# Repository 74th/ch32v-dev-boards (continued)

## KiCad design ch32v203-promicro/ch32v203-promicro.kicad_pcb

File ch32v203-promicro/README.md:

# RISC-V MCU CH32V203 ProMicro Sized Dev Board

The contents of this page include the KiCad files in this repository, as well as kits sold by Booth and finished products sold by Switch Science.

Please check [Documents](#documents) for schematics, bill of materials, pin maps, etc.

🇯🇵

本ページのコンテンツは、本リポジトリの KiCad ファイル、及び Booth 販売品のキット、スイッチサイエンスでの完成品販売の内容が含まれています。

回路図、部品表、ピンマップ等については、[Documents](#documents)を確認ください。

- [CH32V203 での開発方法について](#CH32V203-の開発方法)
- キット販売ページ(BOOTH) https://74th.booth.pm/items/4492691

# main features

- Uses RISC-V CH32V203C8T6, resembling STM32.
- Pin configuration with functions similar to ProMicro (UART, I2C, SPI, ADC).
- By pressing the BOOT button while pressing RESET, it enters a mode that allows writing via USB.
- USB1DM/DP already wired to USB Port(USB2 not wired).

🇯🇵

- STM32 に似せた RISC-V CH32V203C8T6 を使用
- ProMicro に近い機能のピン配置（UART、I2C、SPI、ADC）
- BOOT ボタンを押しながら RESET を押すことで、USB で書き込みできるモードに入る
- USB には、USB1DM/DP を配線済み

# How to use 使い方

- There is a BOOT button, and by pressing the BOOT button while holding down RESET(RST), the mode is set to write via USB.
- GND on the left side is changed to SWDIO and SWCLK. Connect WCH-Link to GND, SWDIO, and SWCLK.

🇯🇵

- BOOT ボタンがあり、RESET を押しながら BOOT ボタンを押すことで、USB 経由で書き込めるモードになります。
- 左側の GND を、SWDIO、SWCLK に変更しています。こちらから WCH-Link を用いることで書き込みができるようになります。WCH-Link と GND、SWDIO、SWCLK を接続してください。

# Documents

## CH32V203Micro v1.2.1-2

- v1.2.2 と v1.2.1 の違いは利用した KiCad バージョンの更新と、若干のフットプリントの修正で、部品表、機能に違いはありません。

- semantics [PDF](./docs/ch32v203-promicro-v1.2.1.pdf) [Kicanvas](https://kicanvas.org/?github=https%3A%2F%2Fgithub.com%2F74th%2Fch32v-dev-boards%2Fblob%2Fch32v203promicro%2F1.2.1%2Fch32v203-promicro%2Fch32v203-promicro.kicad_sch)
- PCB
  - 1.2.1 [Kicanvas](https://kicanvas.org/?github=https%3A%2F%2Fgithub.com%2F74th%2Fch32v-dev-boards%2Fblob%2Fch32v203promicro%2F1.2.1%2Fch32v203-promicro%2Fch32v203-promicro.kicad_pcb)
  - 1.2.2 [Kicanvas](https://kicanvas.org/?github=https%3A%2F%2Fgithub.com%2F74th%2Fch32v-dev-boards%2Fblob%2Fch32v203promicro%2F1.2.2%2Fch32v203-promicro%2Fch32v203-promicro.kicad_pcb)

### Pin Map

### new feature

- Anticipating the use of the USB write function, the following changes have been made:
  - The X32Micro v1.2.0 added an SWD 10-pin port, but it was removed in the CH32V203Micro v1.2.1.
  - The X32Micro v1.2.0 removed the BOOT button, but it was re-added in the CH32V203Micro v1.2.1.
  - The X32Micro v1.2.0 added through-holes for BOOT0 and BOOT1, but these were removed. This is because basically only BOOT0 is used.
- Differences from X32Micro v1.1.0:
  - Added CH213K as a USB power protection IC.
  - Added damping resistors to USB DM/DP.
  - Omitted the low-power crystal oscillator (internal RC clock can be used).
  - Pin configuration change.

🇯🇵

- USB で書き込みできる機能を利用する想定で、以下の変更を行いました。
  - X32Micro v1.2.0 では SWD 10 ピンポートを追加しましたが、CH32V203Micro v1.2.1 ではを削除しました。
  - X32Micro v1.2.0 では BOOT ボタンを削除しましたが、CH32V203Micro v1.2.1 では、BOOT ボタンを再度追加しました。
  - X32Micro v1.2.0 では BOOT0、BOOT1 のスルーホールを追加しましたが、削除しました。BOOT0 しか基本的に利用されないためです。
- X32Micro v1.1.0 からの差分
  - USB 電源保護 IC として CH213K を追加
  - USB DM/DP にダンピング抵抗を追加
  - Low Power 用水晶発振器を省略（内蔵 RC クロックが使用可能）
  - ピン配置変更

### 部品表 Parts List

| Reference  | Name                                  | Quantity |
| ---------- | ------------------------------------- | -------- |
| C1, C2     | Capacitor 0805 10uF                   | 2        |
| C3         | Capacitor 0805 1uF                    | 1        |
| C4-C8      | Capacitor 0805 100nF                  | 5        |
| C9, C10    | Capacitor 0805 10-22pF                | 2        |
| D1         | LED 0805 BLUE                         | 1        |
| J1         | USB Type-C Receptacle                 | 1        |
| R1, R2     | Register 0805 5.1kΩ                   | 2        |
| R3, R6, R7 | Register 0805 10kΩ                    | 3        |
| R4, R5     | Register 0805 27Ω                     | 2        |
| SW1, SW2   | Button SKRPABE010                     | 2        |
| U1         | Regulator 3.3V SOT-89 AMS1117-3.3     | 1        |
| U2         | MCU LQFP48 WCH CH32V203C8T6           | 1        |
| U3         | USB Power Protection IC SOT-23 CH213K | 1        |
| Y1         | Crystal 3225 8MHz                     | 1        |

## X32Micro v1.2.0

Please see [https://github.com/74th/x32promicro?tab=readme-ov-file#x32micro-v120](https://github.com/74th/x32promicro?tab=readme-ov-file#x32micro-v120).

## X32Micro v1.1.0

### 部品表 Parts List

| Reference | Parts                                       | Qty |
| --------- | ------------------------------------------- | --- |
| C1-C3, C6 | 0805 Capacitor 100n                         | 4   |
| C4        | 0805 Capacitor 10u                          | 1   |
| C5        | 0805 Capacitor 2.2u                         | 1   |
| C7, C8    | 0805 Capacitor 12p                          | 2   |
| C9, C10   | 0805 Capacitor 22p                          | 2   |
| R1        | 0805 Resister 200                           | 1   |
| R2        | NC or 0805 Resister 10k for BOOT0 Pull Up   | 1   |
| R8        | NC or 0805 Resister 10k for BOOT0 Pull Down | 1   |
| R6-R7     | 0805 Resister 10k                           | 2   |
| R3        | 0805 Resister 0 R                           | 1   |
| R4, R5    | 0805 Resister 5.1k                          | 2   |
| D1        | 0805 LED                                    | 1   |
| J1        | USB2.0 Socket                               | 1   |
| JP1       | Jumper BOOT SW Pull Up / Down               | 1   |
| SW1, SW2  | SW Push                                     | 2   |
| U1        | MCU STM32V103C8T6                           | 1   |
| U2        | SOT-89 Regulator AMS1117-3.3                | 1   |
| Y1        | 3215 Oscillator 32.768k                     | 1   |
| Y2        | 3225 Oscillator 8M                          | 1   |

- CH32V203 など BOOT0 を Pull Up し、BOOT スイッチで GND に繋ぎたい場合
  - R2 を実装してください
  - R8 は未実装 NC にしてください
  - JP1 の中央のランドを △ マークにジャンパしてください
- STM32F103 など BOOT0 を Pull Down し、BOOT スイッチで 3V3 に繋ぎたい場合
  - R2 は未実装 NC にしてください
  - R8 を実装してください
  - JP1 の中央のランドを + マークにジャンパしてください

## CH32V203Micro v1.0.0

- BOOTH 販売ページ
- 回路図 Semantics [docs/ch32v203-promicro-v1.0.0-semantics.pdf](docs/ch32v203-promicro-v1.0.0-semantics.pdf)
- PCB [docs/ch32v203-promicro-v1.0.0-pcb.pdf](docs/ch32v203-promicro-v1.0.0-pcb.pdf)

### 部品表 Parts List

| Reference | Parts                             | num |
| --------- | --------------------------------- | --- |
| C1-C3,C6  | 0805 Capacitor 100nF              | 4   |
| C4        | 0805 Capacitor 10uF               | 1   |
| C5        | 0805 Capacitor 2.2uF              | 1   |
| C7,C8     | 0805 Capacitor 12pF               | 2   |
| C9,C10    | 0805 Capacitor 22pF               | 2   |
| D1        | 0805 LED                          | 1   |
| J1        | USB Type-C Socket                 | 1   |
| J2        | PinHeader                         | 1   |
| J3        | PinHeader                         | 1   |
| R1        | 0805 Register 200R                | 1   |
| R2,R6,R7  | 0805 Register 10kR                | 3   |
| R3        | 0805 Register 0R                  | 1   |
| R4,R5     | 0805 Register 5.1k                | 2   |
| SW1       | SW Push                           | 2   |
| U1        | MCU CH32V203CxT6                  | 1   |
| U2        | SOT-89 3.3V Regulator AMS1117-3.3 | 1   |
| Y1        | 3215 Oscillator 32.768kHz         | 1   |
| Y2        | 3225 Oscillator 8MB               | 1   |

# CH32V203 の開発方法

## CH32V203 のファームウェアの書き込み方法

### 1. USB で書き込み場合

BOOT を押しながら、RESET を押すと、USB で書き込みを受け付けるモードになります。このモード中では、以下のソフトウェアを用いて書き込みが可能です。

- WCHISP Tool(公式) : https://www.wch-ic.com/downloads/WCHISPTool_Setup_exe.html
  - GUI で操作するツール
  - Windows のみ
- wchisp(ch32-rs) : https://github.com/ch32-rs/wchisp
  - CLI ツール

私 74th としては、wchisp が、Linux でも動作するため、便利でお勧めです。以下のようにして、書き込みます。

```
wchisp flash release/ch32v203c8t6.elf
```

### 2. WCH-Link を用いる場合

WCH-Link と SWDIO、SWCLK を接続してください。

WCH-Link を用いる場合の書き込みソフトウェアとして、以下があります。

- WCH-LinkUtility(公式) : https://www.wch.cn/downloads/WCH-LinkUtility_ZIP.html
  - GUI で操作するツール
  - Windows のみ
- minichlink(ch32v003fun) : https://github.com/cnlohr/ch32v003fun/tree/master/minichlink
  - CLI ツール
- wlink(ch32-rs) : https://github.com/ch32-rs/wlink
  - CLI ツール
- OpenOCD(WCH によるフォーク): MounRiverStudio に含まれる http://www.mounriver.com/download
  - CLI ツール

74th としては、wlink が、Linux でも動作するため、便利でお勧めです。

```
wlink flash release/ch32v203c8t6.elf
```

## CH32V203 の開発環境

PlatformIO(VS Code)を使った開発の方法を記事にしています

> WCH の RISC-V マイコン CH32V を公式 SDK を使って、VS Code の PlatformIO で開発する - @74th の制作ログ
>
> https://74th.hateblo.jp/entry/ch32v-platformio

CH32V203 の開発フレームワークとして以下が利用可能です。

- 公式 SDK: https://github.com/openwch/ch32v20x/tree/main/C%2B%2B/Use%20MRS%20Create%20C%2B%2B%20project-example/CH32V203C8T6%2B%2B
  - C/C++
  - STM32 の古い SDK 似
- ch32-rs: https://github.com/ch32-rs/ch32-rs
  - Rust のペリフェラルアクセスクレート
- WCH 提供 Arduino: https://github.com/openwch/arduino_core_ch32

開発環境としては、以下が利用できます。

- MounRiverStudio(公式): http://www.mounriver.com/download
  - 公式 SDK を利用
  - Windows、Linux のみ
- PlatformIO(コミュニティメンテ) : https://github.com/Community-PIO-CH32V/platform-ch32v
  - 公式 SDK を利用
  - MounRiverStudio に含まれる GNU ライセンスの gcc、OpenOCD 等を取り込んでいる
  - gcc、OpenOCD は x64 のみ（ARM CPU では動作不可）
- Rust(ch32v-rs 利用)
- Arduino IDE: https://github.com/openwch/arduino_core_ch32
- 公式 SDK 用 Makefile テンプレート: https://github.com/cjacker/ch32v_evt_makefile_gcc_project_template

74th としては PlatformIO が、環境構築がお手軽でお勧めです。ただし、AMD64 CPU でないと動作しません。

CH32V203 は、RV32IMAC に独自拡張命令を含んだ RV32IMACXW という命令セットを使っています。そのため、公式が提供する GCC でないと正常にコンパイルできないことがあります。

## 開発方法についてのブログ記事等情報

### 74th のブログ記事

- WCH の RISC-V マイコン CH32V を公式 SDK を使って、VS Code の PlatformIO で開発する https://74th.hateblo.jp/entry/ch32v-platformio
- WCH の RISC-V MCU CH32V203 を Rust で L チカする https://74th.hateblo.jp/entry/2022/12/22/223956

### その他記事

- オープンソースツールチェインでの CH32V の開発方法（英語） https://github.com/cjacker/opensource-toolchain-ch32v
- VSCode+PlatformIO で RISC-V CH32V203 マイコンの開発環境を構築 https://zenn.dev/usagi1975/articles/2023-09-30-0002_ch32v-platformio

### 公式ドキュメント

- データシート https://www.wch-ic.com/downloads/CH32V20x_30xDS0_PDF.html
- リファレンスマニュアル https://www.wch-ic.com/downloads/CH32FV2x_V3xRM_PDF.html
- C/C++ SDK https://github.com/openwch/ch32v20x/tree/main/C%2B%2B/Use%20MRS%20Create%20C%2B%2B%20project-example/CH32V203C8T6%2B%2B

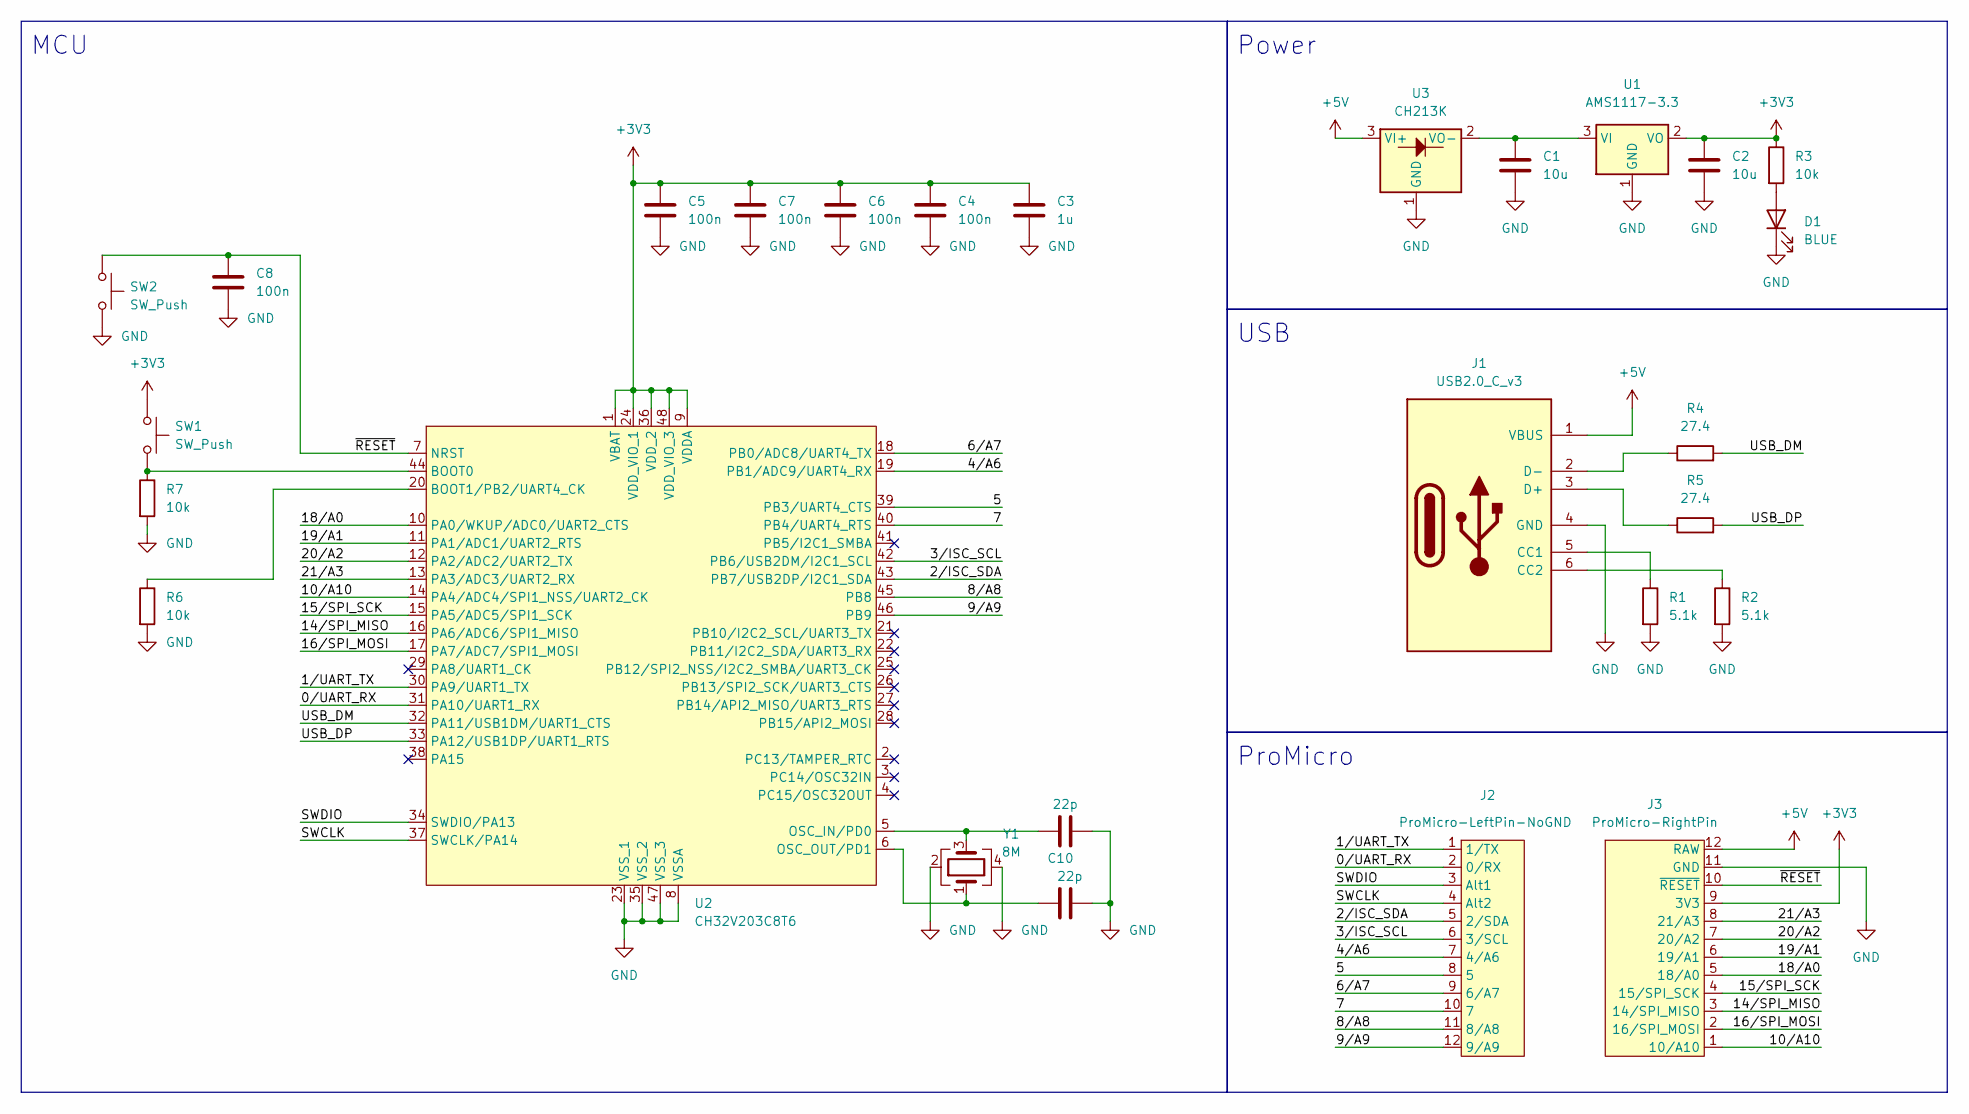
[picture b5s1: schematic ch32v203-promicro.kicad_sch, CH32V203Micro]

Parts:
C1, C2: 10u; Capacitor_0805_2012
C3: 1u; Capacitor_0805_2012
C4, C5, C6, C7, C8: 100n; Capacitor_0805_2012
C9, C10: 22p; Capacitor_0805_2012
D1: BLUE; LED_0805_2012
J1: USB2.0_C_v3; Connector_USB-C-Receptacle_SMT_12-Pin_Simple
J2: ProMicro-LeftPin-NoGND; PinOut_ProMicro-LIKE_LEFT_NO-GND
J3: ProMicro-RightPin; PinOut_ProMicro-LIKE_RIGHT
R1, R2: 5.1k; Register_0805_2012
R3, R6, R7: 10k; Register_0805_2012
R4, R5: 27.4; Register_0805_2012
SW1, SW2: SW_Push; Switch_SKRPABE010
U1: AMS1117-3.3; Package_SOT-89-3
U2: CH32V203C8T6; Package_LQFP-48_7x7mm_P0.5mm
U3: CH213K; Package_SOT-23
Y1: 8M; Crystal_SMD_3225-4Pin_3.2x2.5mm_HandSoldering

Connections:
+3V3: C2.1, C3.1, C4.1, C5.1, C6.1, C7.1, J3.9 (3V3), R3.1, SW1.1, U1.2 (VO), U2.1 (VBAT), U2.9 (VDDA), U2.24 (VDD_VIO_1), U2.36 (VDD_2), U2.48 (VDD_VIO_3)
+5V: J1.1 (VBUS), J3.12 (RAW), U3.3 (VI+)
/0/UART_RX: J2.2 (0/RX), U2.31 (PA10/UART1_RX)
/1/UART_TX: J2.1 (1/TX), U2.30 (PA9/UART1_TX)
/2/ISC_SDA: J2.5 (2/SDA), U2.43 (PB7/USB2DP/I2C1_SDA)
/3/ISC_SCL: J2.6 (3/SCL), U2.42 (PB6/USB2DM/I2C1_SCL)
/4/A6: J2.7 (4/A6), U2.19 (PB1/ADC9/UART4_RX)
/5: J2.8 (5), U2.39 (PB3/UART4_CTS)
/6/A7: J2.9 (6/A7), U2.18 (PB0/ADC8/UART4_TX)
/7: J2.10 (7), U2.40 (PB4/UART4_RTS)
/8/A8: J2.11 (8/A8), U2.45 (PB8)
/9/A9: J2.12 (9/A9), U2.46 (PB9)
/10/A10: J3.1 (10/A10), U2.14 (PA4/ADC4/SPI1_NSS/UART2_CK)
/14/SPI_MISO: J3.3 (14/SPI_MISO), U2.16 (PA6/ADC6/SPI1_MISO)
/15/SPI_SCK: J3.4 (15/SPI_SCK), U2.15 (PA5/ADC5/SPI1_SCK)
/16/SPI_MOSI: J3.2 (16/SPI_MOSI), U2.17 (PA7/ADC7/SPI1_MOSI)
/18/A0: J3.5 (18/A0), U2.10 (PA0/WKUP/ADC0/UART2_CTS)
/19/A1: J3.6 (19/A1), U2.11 (PA1/ADC1/UART2_RTS)
/20/A2: J3.7 (20/A2), U2.12 (PA2/ADC2/UART2_TX)
/21/A3: J3.8 (21/A3), U2.13 (PA3/ADC3/UART2_RX)
/SWCLK: J2.4 (Alt2), U2.37 (SWCLK/PA14)
/SWDIO: J2.3 (Alt1), U2.34 (SWDIO/PA13)
/USB_DM: R4.2, U2.32 (PA11/USB1DM/UART1_CTS)
/USB_DP: R5.2, U2.33 (PA12/USB1DP/UART1_RTS)
/~RESET: C8.1, J3.10 (~RESET), SW2.1, U2.7 (NRST)
GND: C1.2, C2.2, C3.2, C4.2, C5.2, C6.2, C7.2, C8.2, C9.2, C10.2, D1.1 (K), J1.4 (GND), J3.11 (GND), R1.2, R2.2, R6.2, R7.2, SW2.2, U1.1 (GND), U2.8 (VSSA), U2.23 (VSS_1), U2.35 (VSS_2), U2.47 (VSS_3), U3.1 (GND), Y1.2, Y1.4
unnamed: D1.2 (A), R3.2
unnamed: J1.5 (CC1), R1.1
unnamed: J1.6 (CC2), R2.1
unnamed: J1.3 (D+), R5.1
unnamed: J1.2 (D-), R4.1
unnamed: C1.1, U1.3 (VI), U3.2 (VO-)
unnamed: R7.1, SW1.2, U2.44 (BOOT0)
unnamed: R6.1, U2.20 (BOOT1/PB2/UART4_CK)
unnamed: C9.1, U2.5 (OSC_IN/PD0), Y1.3
unnamed: C10.1, U2.6 (OSC_OUT/PD1), Y1.1

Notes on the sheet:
USB
ProMicro
MCU
Power

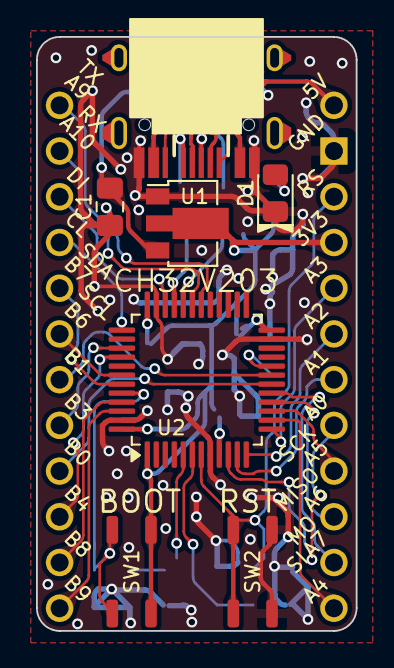
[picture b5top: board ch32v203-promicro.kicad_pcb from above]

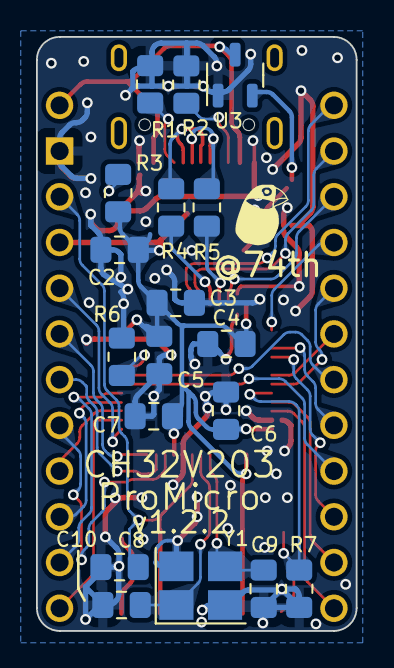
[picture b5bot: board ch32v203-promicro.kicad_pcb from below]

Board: 2 copper layers, 17.8 x 33.0 mm, 28 parts (19 on the bottom side), 36 nets.

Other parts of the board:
MISC-ICON: LOGO; 74th-4mm

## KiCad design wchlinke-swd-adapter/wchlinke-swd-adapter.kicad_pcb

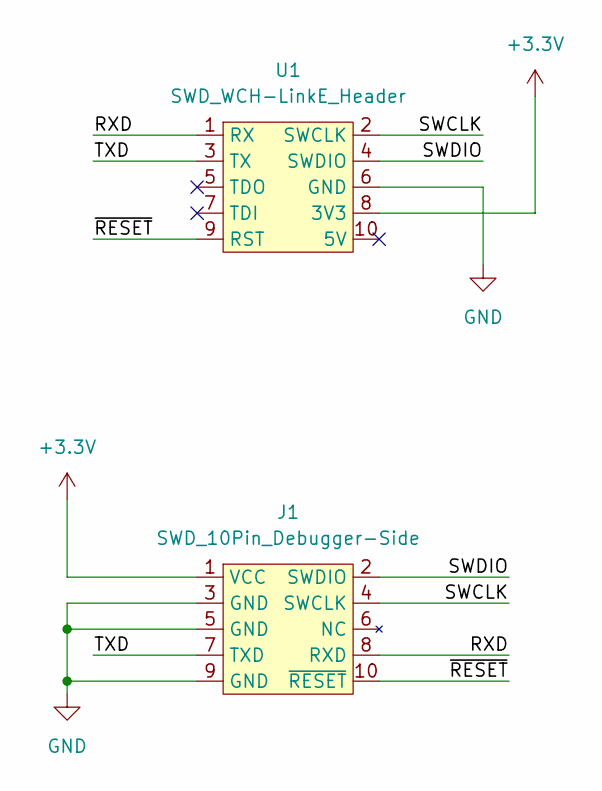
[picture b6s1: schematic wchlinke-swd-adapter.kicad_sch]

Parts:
J1: SWD_10Pin_Debugger-Side; Connector_BoxPinHeader_2x05_P1.27mm
U1: SWD_WCH-LinkE_Header; PinOut_Side_2x5P_Left_Reverse

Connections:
+3.3V: J1.1 (VCC), U1.8 (3V3)
/RXD: J1.8 (RXD), U1.1 (RX)
/SWCLK: J1.4 (SWCLK), U1.2 (SWCLK)
/SWDIO: J1.2 (SWDIO), U1.4 (SWDIO)
/TXD: J1.7 (TXD), U1.3 (TX)
/~RESET: J1.10 (~RESET), U1.9 (RST)
GND: J1.3 (GND), J1.5 (GND), J1.9 (GND), U1.6 (GND)

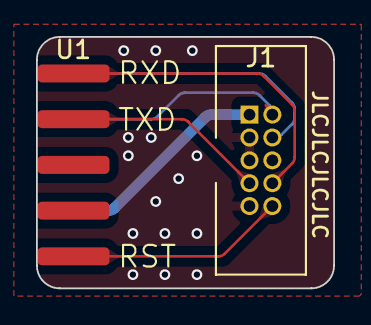
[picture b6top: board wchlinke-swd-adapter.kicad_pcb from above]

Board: 2 copper layers, 16.5 x 14.0 mm, 3 parts (1 on the bottom side), 7 nets.

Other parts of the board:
MISC-ICON: LOGO; Logo_74th_4mm

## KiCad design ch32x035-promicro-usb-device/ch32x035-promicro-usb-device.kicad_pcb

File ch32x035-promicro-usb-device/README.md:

# CH32X035 for USB-Device ProMicro

## v1.0.0

### BOM

| Reference | Name                                     | Quantity |
| --------- | ---------------------------------------- | -------- |
| C1, C2    | Capacitor 0603 10uF                      | 2        |
| C3        | Capacitor 0603 1uF                       | 1        |
| C4        | Capacitor 0603 100nF                     | 1        |
| D1        | LED 0805 BLUE                            | 1        |
| J1        | USB Type-C Receptacle                    | 1        |
| J2        | Box Pin Header 2x5 Pitch 1.27mm          | 1        |
| JP1       | Jumper Jumper_2_Open                     | 1        |
| R1, R2    | Register 0603 5.1kΩ                      | 2        |
| R3        | Register 0603 100kΩ                      | 1        |
| R4        | Register 0603 1.5kΩ                      | 1        |
| R5, R8    | Register 0603 10kΩ                       | 2        |
| R6, R7    | Register 0603 27Ω                        | 2        |
| SW1       | Button SKRPABE010                        | 1        |
| U1        | Regulator 3.3V SOT-89 AMS1117-3.3        | 1        |
| U2        | MCU QFN28 WCH CH32X035G8U6               | 1        |
| U3        | USB Power Protection IC SOT-23-6L CH217K | 1        |

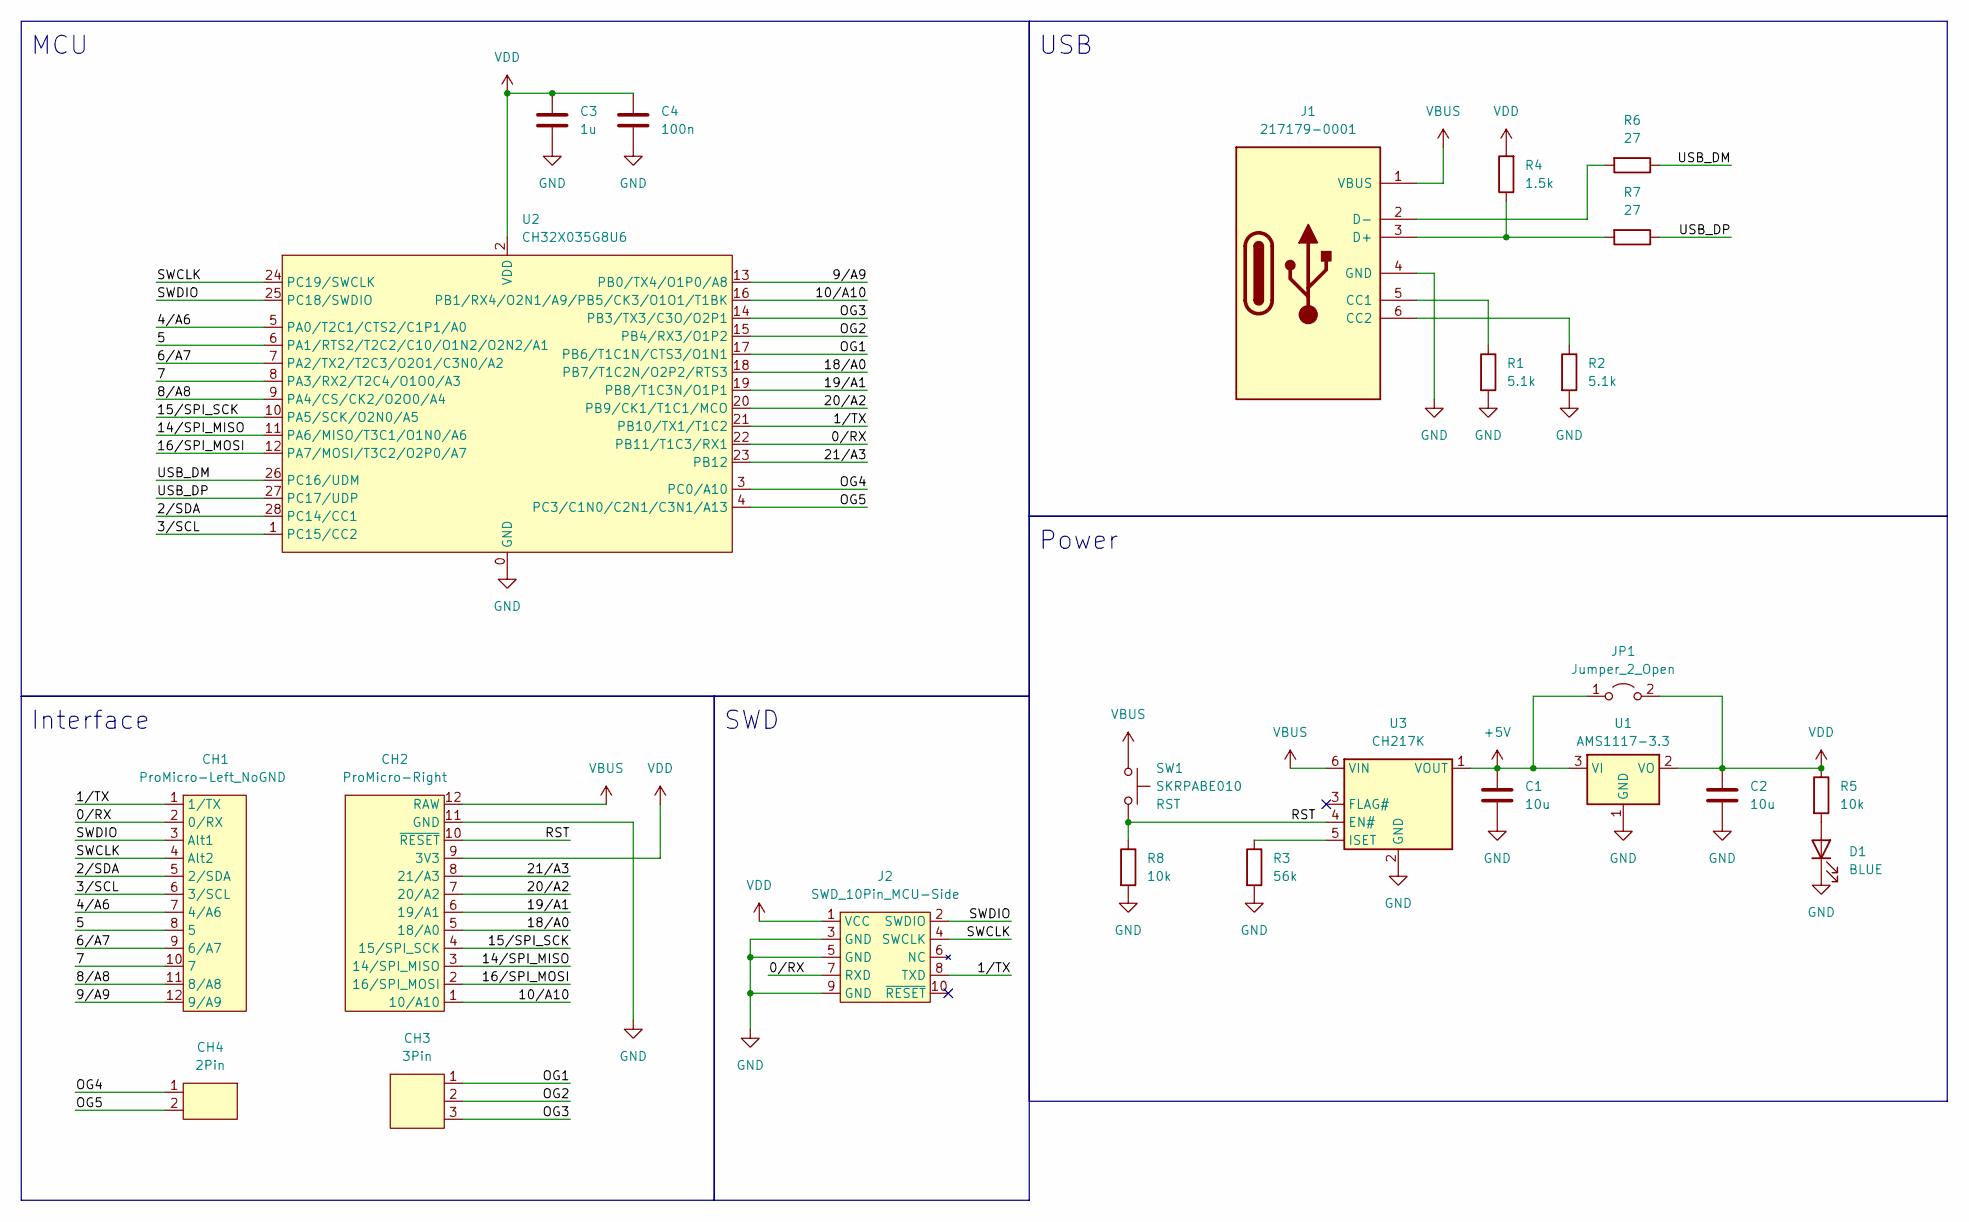
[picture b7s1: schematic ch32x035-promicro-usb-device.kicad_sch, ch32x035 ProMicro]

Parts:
C1, C2: 10u; Capacitor_0603_1608
C3: 1u; Capacitor_0603_1608
C4: 100n; Capacitor_0603_1608
CH1: ProMicro-Left_NoGND; PinOut_ProMicro-LIKE_LEFT_NO-GND
CH2: ProMicro-Right; PinOut_ProMicro-LIKE_RIGHT
CH3: 3Pin; PinOut_3Pin
CH4: 2Pin; PinOut_2Pin
D1: BLUE; LED_0805_2012
J1: 217179-0001; Connector_USB-C-Receptacle_SMT_12-Pin_Simple
J2: SWD_10Pin_MCU-Side; Connector_HalfPinHeader_SWD
JP1: Jumper_2_Open; SolderJumper-2_P1.3mm_Open_RoundedPad1.0x1.5mm
R1, R2: 5.1k; Register_0603_1608
R3: 56k; Register_0603_1608
R4: 1.5k; Register_0603_1608
R5, R8: 10k; Register_0603_1608
R6, R7: 27; Register_0603_1608
SW1: SKRPABE010; PushButton_SKRPABE010
U1: AMS1117-3.3; SOT-89-3
U2: CH32X035G8U6; Package_QFN-28-1EP_4x4mm_P0.4mm_EP2.8x2.8mm
U3: CH217K; SOT-23-6

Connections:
+5V: C1.1, JP1.1 (A), U1.3 (VI), U3.1 (VOUT)
/0/RX: CH1.2 (0/RX), J2.7 (RXD), U2.22 (PB11/T1C3/RX1)
/1/TX: CH1.1 (1/TX), J2.8 (TXD), U2.21 (PB10/TX1/T1C2)
/2/SDA: CH1.5 (2/SDA), U2.28 (PC14/CC1)
/3/SCL: CH1.6 (3/SCL), U2.1 (PC15/CC2)
/4/A6: CH1.7 (4/A6), U2.5 (PA0/T2C1/CTS2/C1P1/A0)
/5: CH1.8 (5), U2.6 (PA1/RTS2/T2C2/C10/O1N2/O2N2/A1)
/6/A7: CH1.9 (6/A7), U2.7 (PA2/TX2/T2C3/O2O1/C3N0/A2)
/7: CH1.10 (7), U2.8 (PA3/RX2/T2C4/O1O0/A3)
/8/A8: CH1.11 (8/A8), U2.9 (PA4/CS/CK2/O2O0/A4)
/9/A9: CH1.12 (9/A9), U2.13 (PB0/TX4/O1P0/A8)
/10/A10: CH2.1 (10/A10), U2.16 (PB1/RX4/O2N1/A9/PB5/CK3/O1O1/T1BK)
/14/SPI_MISO: CH2.3 (14/SPI_MISO), U2.11 (PA6/MISO/T3C1/O1N0/A6)
/15/SPI_SCK: CH2.4 (15/SPI_SCK), U2.10 (PA5/SCK/O2N0/A5)
/16/SPI_MOSI: CH2.2 (16/SPI_MOSI), U2.12 (PA7/MOSI/T3C2/O2P0/A7)
/18/A0: CH2.5 (18/A0), U2.18 (PB7/T1C2N/O2P2/RTS3)
/19/A1: CH2.6 (19/A1), U2.19 (PB8/T1C3N/O1P1)
/20/A2: CH2.7 (20/A2), U2.20 (PB9/CK1/T1C1/MCO)
/21/A3: CH2.8 (21/A3), U2.23 (PB12)
/OG1: CH3.1, U2.17 (PB6/T1C1N/CTS3/O1N1)
/OG2: CH3.2, U2.15 (PB4/RX3/O1P2)
/OG3: CH3.3, U2.14 (PB3/TX3/C3O/O2P1)
/OG4: CH4.1, U2.3 (PC0/A10)
/OG5: CH4.2, U2.4 (PC3/C1N0/C2N1/C3N1/A13)
/RST: CH2.10 (~RESET), R8.1, SW1.2, U3.4 (EN#)
/SWCLK: CH1.4 (Alt2), J2.4 (SWCLK), U2.24 (PC19/SWCLK)
/SWDIO: CH1.3 (Alt1), J2.2 (SWDIO), U2.25 (PC18/SWDIO)
/USB_DM: R6.1, U2.26 (PC16/UDM)
/USB_DP: R7.1, U2.27 (PC17/UDP)
GND: C1.2, C2.2, C3.2, C4.2, CH2.11 (GND), D1.1 (K), J1.4 (GND), J2.3 (GND), J2.5 (GND), J2.9 (GND), R1.2, R2.2, R3.2, R8.2, U1.1 (GND), U2.0 (GND), U3.2 (GND)
unnamed: D1.2 (A), R5.2
unnamed: J1.5 (CC1), R1.1
unnamed: J1.6 (CC2), R2.1
unnamed: J1.3 (D+), R4.1, R7.2
unnamed: J1.2 (D-), R6.2
unnamed: R3.1, U3.5 (ISET)
VBUS: CH2.12 (RAW), J1.1 (VBUS), SW1.1, U3.6 (VIN)
VDD: C2.1, C3.1, C4.1, CH2.9 (3V3), J2.1 (VCC), JP1.2 (B), R4.2, R5.1, U1.2 (VO), U2.2 (VDD)

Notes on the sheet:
MCU
USB
Power
Interface
SWD

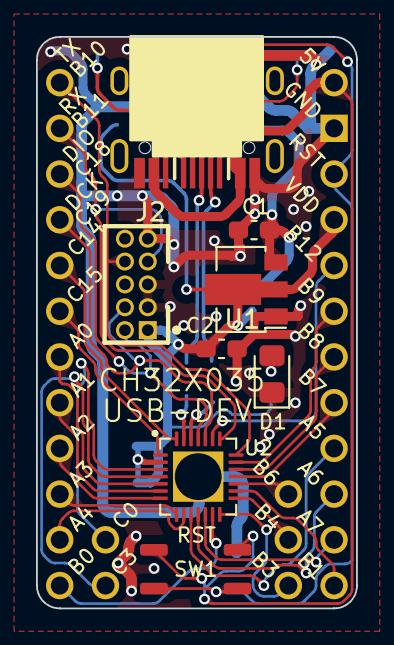
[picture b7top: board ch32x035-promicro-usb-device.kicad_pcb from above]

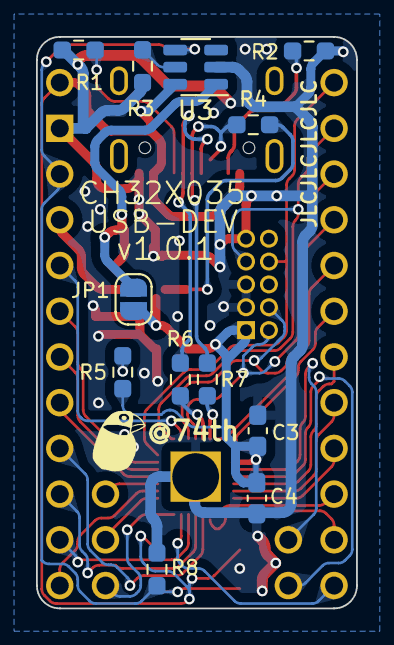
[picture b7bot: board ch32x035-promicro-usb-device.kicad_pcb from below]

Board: 2 copper layers, 17.8 x 31.8 mm, 26 parts (14 on the bottom side), 38 nets.

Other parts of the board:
MISC-ACCOUNTTEXT: Logo_74th_text
MISC-ICON: LOGO; Logo_74th_4mm

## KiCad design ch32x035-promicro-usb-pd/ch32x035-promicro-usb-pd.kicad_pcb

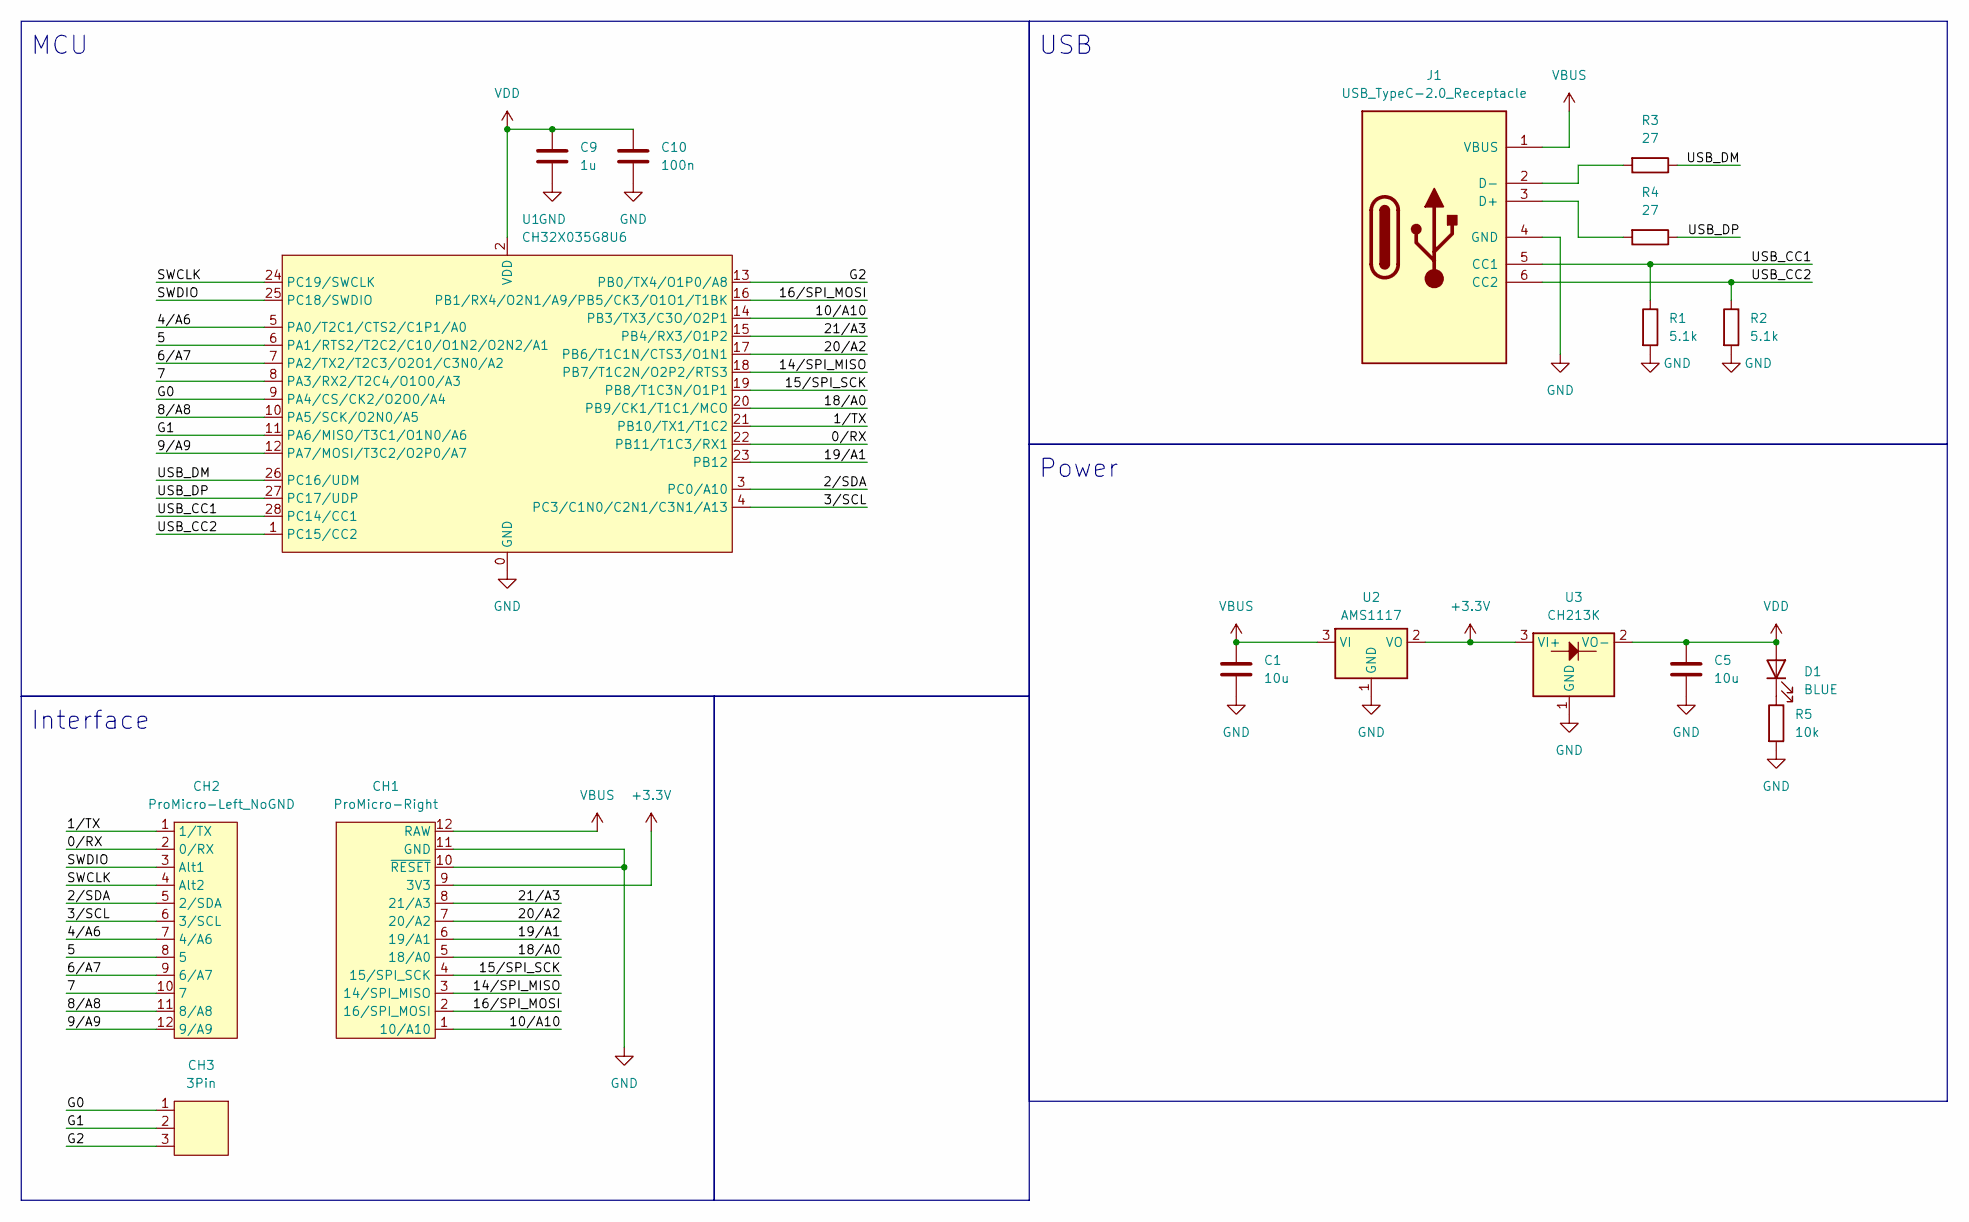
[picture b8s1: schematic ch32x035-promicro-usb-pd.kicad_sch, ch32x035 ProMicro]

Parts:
C1, C5: 10u; Capacitor_0805_2012
C9: 1u; Capacitor_0805_2012
C10: 100n; Capacitor_0805_2012
CH1: ProMicro-Right; PinOut_ProMicro-LIKE_RIGHT
CH2: ProMicro-Left_NoGND; PinOut_ProMicro-LIKE_LEFT_NO-GND
CH3: 3Pin; PinOut_3Pin
D1: BLUE; LED_0805_2012
J1: USB_TypeC-2.0_Receptacle; Connector_USB-C-Receptacle_SMT_12-Pin_Simple
R1, R2: 5.1k; Register_0805_2012
R3, R4: 27; Register_0805_2012
R5: 10k; Register_0805_2012
U1: CH32X035G8U6; Package_QFN-28-1EP_4x4mm_P0.4mm_EP2.8x2.8mm
U2: AMS1117; SOT-89-3
U3: CH213K; SOT-23

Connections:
+3.3V: CH1.9 (3V3), U2.2 (VO), U3.3 (VI+)
/0/RX: CH2.2 (0/RX), U1.22 (PB11/T1C3/RX1)
/1/TX: CH2.1 (1/TX), U1.21 (PB10/TX1/T1C2)
/2/SDA: CH2.5 (2/SDA), U1.3 (PC0/A10)
/3/SCL: CH2.6 (3/SCL), U1.4 (PC3/C1N0/C2N1/C3N1/A13)
/4/A6: CH2.7 (4/A6), U1.5 (PA0/T2C1/CTS2/C1P1/A0)
/5: CH2.8 (5), U1.6 (PA1/RTS2/T2C2/C10/O1N2/O2N2/A1)
/6/A7: CH2.9 (6/A7), U1.7 (PA2/TX2/T2C3/O2O1/C3N0/A2)
/7: CH2.10 (7), U1.8 (PA3/RX2/T2C4/O1O0/A3)
/8/A8: CH2.11 (8/A8), U1.10 (PA5/SCK/O2N0/A5)
/9/A9: CH2.12 (9/A9), U1.12 (PA7/MOSI/T3C2/O2P0/A7)
/10/A10: CH1.1 (10/A10), U1.14 (PB3/TX3/C3O/O2P1)
/14/SPI_MISO: CH1.3 (14/SPI_MISO), U1.18 (PB7/T1C2N/O2P2/RTS3)
/15/SPI_SCK: CH1.4 (15/SPI_SCK), U1.19 (PB8/T1C3N/O1P1)
/16/SPI_MOSI: CH1.2 (16/SPI_MOSI), U1.16 (PB1/RX4/O2N1/A9/PB5/CK3/O1O1/T1BK)
/18/A0: CH1.5 (18/A0), U1.20 (PB9/CK1/T1C1/MCO)
/19/A1: CH1.6 (19/A1), U1.23 (PB12)
/20/A2: CH1.7 (20/A2), U1.17 (PB6/T1C1N/CTS3/O1N1)
/21/A3: CH1.8 (21/A3), U1.15 (PB4/RX3/O1P2)
/G0: CH3.1, U1.9 (PA4/CS/CK2/O2O0/A4)
/G1: CH3.2, U1.11 (PA6/MISO/T3C1/O1N0/A6)
/G2: CH3.3, U1.13 (PB0/TX4/O1P0/A8)
/SWCLK: CH2.4 (Alt2), U1.24 (PC19/SWCLK)
/SWDIO: CH2.3 (Alt1), U1.25 (PC18/SWDIO)
/USB_CC1: J1.5 (CC1), R1.1, U1.28 (PC14/CC1)
/USB_CC2: J1.6 (CC2), R2.1, U1.1 (PC15/CC2)
/USB_DM: R3.1, U1.26 (PC16/UDM)
/USB_DP: R4.1, U1.27 (PC17/UDP)
GND: C1.2, C5.2, C9.2, C10.2, CH1.10 (~RESET), CH1.11 (GND), J1.4 (GND), R1.2, R2.2, R5.2, U1.0 (GND), U2.1 (GND), U3.1 (GND)
unnamed: D1.1 (K), R5.1
unnamed: J1.3 (D+), R4.2
unnamed: J1.2 (D-), R3.2
VBUS: C1.1, CH1.12 (RAW), J1.1 (VBUS), U2.3 (VI)
VDD: C5.1, C9.1, C10.1, D1.2 (A), U1.2 (VDD), U3.2 (VO-)

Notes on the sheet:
MCU
USB
Power
Interface

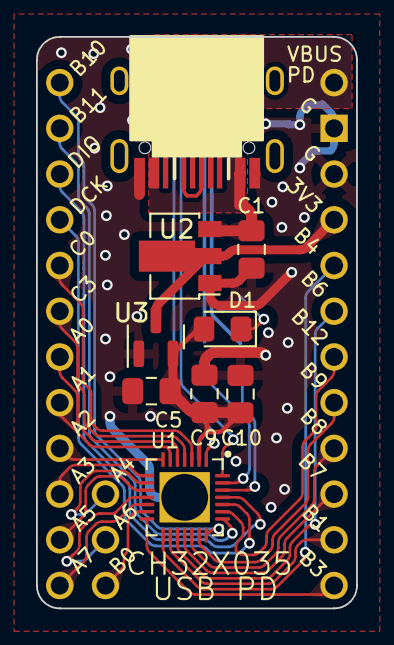
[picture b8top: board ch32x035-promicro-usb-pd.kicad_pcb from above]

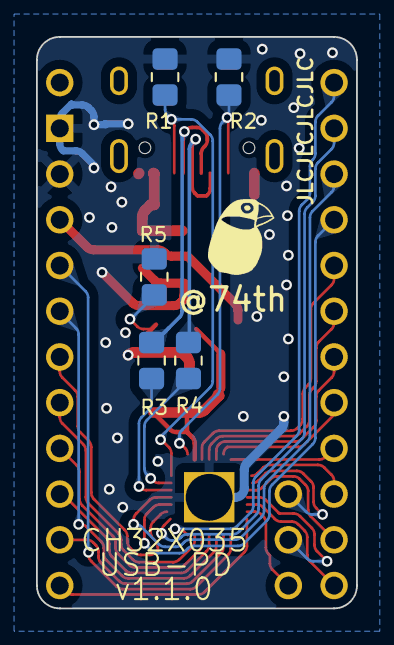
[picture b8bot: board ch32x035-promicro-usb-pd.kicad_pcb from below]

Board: 2 copper layers, 17.8 x 31.8 mm, 19 parts (7 on the bottom side), 34 nets.

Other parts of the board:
MISC-ACCOUNTTEXT: Logo_74th_text
MISC-ICON: LOGO; Logo_74th_5mm

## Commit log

2022-12-24 add symbols
2022-12-24 add symbol
2022-12-25 promicro
2022-12-25 ch32v203 promicro
2022-12-26 ch32v203micro
2022-12-26 ch32v203micro v1.0.0
2022-12-26 ch32v001 mincro
2022-12-27 ch32v003micro v1.0.0
2023-01-24 stm32
2023-01-28 x32micro v1.1.0
2023-03-01 ch32v003promicro/1.0.0
2023-03-26 add DataSheet
2023-08-17 ch32v003promicro/1.1.0
2023-09-15 v1.2.0
2023-09-18 add ch32x035
2023-09-27 ch32v203 promicro v1.2.1
2023-09-28 ch32x035-usb-device
2023-10-01 ch32x035
2023-10-17 fix SWDIO/SWCLK
2023-11-10 ch32x035-usb-pd
2023-11-10 ch32v003promicro/1.2.0
2024-01-04 ファイル移動
2024-01-11 pinout picture
2024-01-13 update document
2024-01-13 WCH LinkE SWD Adapter
2024-08-02 update kicad version
2025-02-24 ch32v00x-soic8/1.0.0
2025-02-24 ch32v006-full/1.0.0
2025-03-17 ch32v003promicto/1.3.0
2025-03-30 fix silk
2025-03-30 Add color specifications to PCB layers and update README with images
2025-05-24 ch32v00x/v1.3.1
2025-05-24 revert to ch32v003 v1.2.0
2025-05-24 add photo
2025-07-28 rvswdio-programer/1.0.0
2025-08-10 it works
2025-08-10 spell misstake
2025-08-10 remove lock file for rvswdio-programer
2025-08-23 rvswdio-programer/1.0.1
